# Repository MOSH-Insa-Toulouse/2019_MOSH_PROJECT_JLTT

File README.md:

# 2019_MOSH_PROJECT_JLTT : Kicad and Arduino LoraProject for SMART GAS sensor
> Loan Revardel / Jérémy Turi / Théo Zanchi / Thomas Lautrédou

#### <em> Key-words: </em> ```Arduino```, ```KiCad```, ```The Thing Network```, ```LoRa```, ```Node-RED```, ```IoT```, ```Gas sensor```.

This project was carried out as part of ISS (Innovative Smart Systems) 5th year at INSA Toulouse. The objective was to develop a gas sensor able to detect dangerous gases for human beings and communicating datas via Lora. Then, using the Node-RED software, we retrieved the data and displayed it on a graphical interface that the user could understand. As soon as a dangerous gas is detected, a buzzer is triggered to warn the user and avoid potential casualties. 

# Content of the Project

This repository contains : 
<ul>
<li><strong>KiCad files</strong> : We developed a shield for the gas sensor compatible with Arduino Uno (using <a href="http://kicad-pcb.org/">KiCad</a>) </li>
<li><strong>Arduino SW files</strong> : The source code we implemented on the microcontroller <a href="https://fr.rs-online.com/web/p/products/7589339?cm_mmc=FR-PLA-DS3A-_-google-_-CSS_FR_FR_(FR:Whoop!)+Semi-conducteurs_Control-_-(FR:Whoop!)+Kits+de+d%C3%A9veloppement+pour+processeurs+et+microcontr%C3%B4leurs-_-PRODUCT_GROUP&matchtype=&pla-391040009911&gclid=CjwKCAiAlO7uBRANEiwA_vXQ-7CN3iR2N3csU5tjIIjQNIGa3bsX8twG7D_S9v6flhEkI08b6nLumxoCnKcQAvD_BwE&gclsrc=aw.ds"> ATMEGA328 </a> (using <a href="https://www.arduino.cc/">Arduino IDE</a>)</li>
<li>A <strong>Node-RED dashboard</strong> to display datas retrieved from the gas sensor (using <a href="https://nodered.org/">Node-RED</a>)</li>
</ul>

# Overall components presentation
The goal of the project was to develop a prototype able to detect high dangerous gas concentration in a specific area. In this situation, a siren is triggered to alert people and avoid casualties. 

To do so, we used :
<ul>
<li>A <a href="https://store.arduino.cc/arduino-uno-rev3">Arduino Uno Board</a></li>
<li>A LoRa chip <a href="https://www.microchip.com/wwwproducts/en/RN2483">RN2483A</a></li>
<li>A <a href="http://wiki.seeedstudio.com/Grove-Gas_Sensor-MQ9/">Grove Gas Sensor (MQ9)</a></li>
<li>A potentiometer</li>
<li>A transistor <a href="http://www.vishay.com/docs/91291/91291.pdf">IRFZ44</a></li>
</ul>

### Dashboard

Then after creating a TTN application and registering our device, we used a ttn uplink node to receive the data sent to our TTN application. Finally, with some basic functions and chart blocs, we were able to display in a dashboard all the data in real time. You can find on the following figures the Node-Red flow and dashboard:

### Energy consumption

During our smart device realization, we studied the energy consumption in order to optimize it. We found that we were consuming 355mA and 370mA during an emission. That is why we chose to define a sleep cycle. Indeed, every 8 seconds, our smart device wake up, read the sensor value and send it to TTN. To realize this, we used an Arduino library by convenience and lack of time:

This sleep cycle allows a great reduction of energy consumption and an increasing of battery lifetime.

## KiCad

In this repository, you can find KiCad files of our project. We designed an Arduino shield based on the sensor we produced at the AIME laboratory. This shield is composed of the sensor, a buzzer, a NRF2483 LoRa ship and an adapter circuit for the gas sensor. You can see on the following figure the schematics we designed with KiCad:

After the schematics design, we exported the net file and realized the PCB routing that you can find with the following figures:

Finally, we exported a 3d representation of our shield thanks to KiCad:

## Conclusion

During this whole module, we were able to realize an electronic product from scratch. Indeed, from the sensor creation to the shield design and software programming, we had to mobilize several skills. Our team was composed of people with different background. That point helped us to dispatch the tasks and learn from the other experience.

To improve our project, we could for example design a PCB of a smaller size by using SMD instead of through-hole ones. Also, our PCB is only composed of the sensing and acting part of the device, a great think can be to integrate directly a micro-controller like an atmega328p in our PCB. The question of the battery and energy harvesting can be also asked and finally, we can use, to develop the dashboard, a different technology instead of Node-Red which is quite limiting.

To conclude, the whole process of sensor creation at the AIME, the PCB design with KiCad and the building of smart device during the MOSH module was a really interesting project related to IOT.

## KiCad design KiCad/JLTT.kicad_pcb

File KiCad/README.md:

# 2019_MOSH_PROJECT_JLTT : Kicad and Arduino LoraProject for SMART GAS sensor
> Loan Revardel / Jérémy Turi / Théo Zanchi / Thomas Lautrédou

#### <em> Key-words: </em> ```Arduino```, ```KiCad```, ```The Thing Network```, ```LoRa```, ```Node-RED```, ```IoT```, ```Gas sensor```.

This project was carried out as part of ISS (Innovative Smart Systems) 5th year at INSA Toulouse. The objective was to develop a gas sensor able to detect dangerous gases for human beings and communicating datas via Lora. Then, using the Node-RED software, we retrieved the data and displayed it on a graphical interface that the user could understand. As soon as a dangerous gas is detected, a buzzer is triggered to warn the user and avoid potential casualties. 

# Content of the Project

This repository contains : 
<ul>
<li><strong>KiCad files</strong> : We developed a shield for the gas sensor compatible with Arduino Uno (using [KiCad](http://kicad-pcb.org/))</li>
<li><strong>Arduino SW files</strong></li>
<li>A <strong>Node-RED dashboard</strong> to display datas retrieved from the gas sensor</li>
</ul>

Conso : 355mA (fonctionnement normal) et 370mA (fonctionnement en émission)

Il faut mettre un Nmos en Not Gate => Quand y'a un 0 le transistor est ouvert et le gaz sensor est relié à Vdd grâce à la résistance de pull-up, et quand on met 1 le transistor est passant et donc la tension aux bornes du Gaz sensor est amenée à 0.

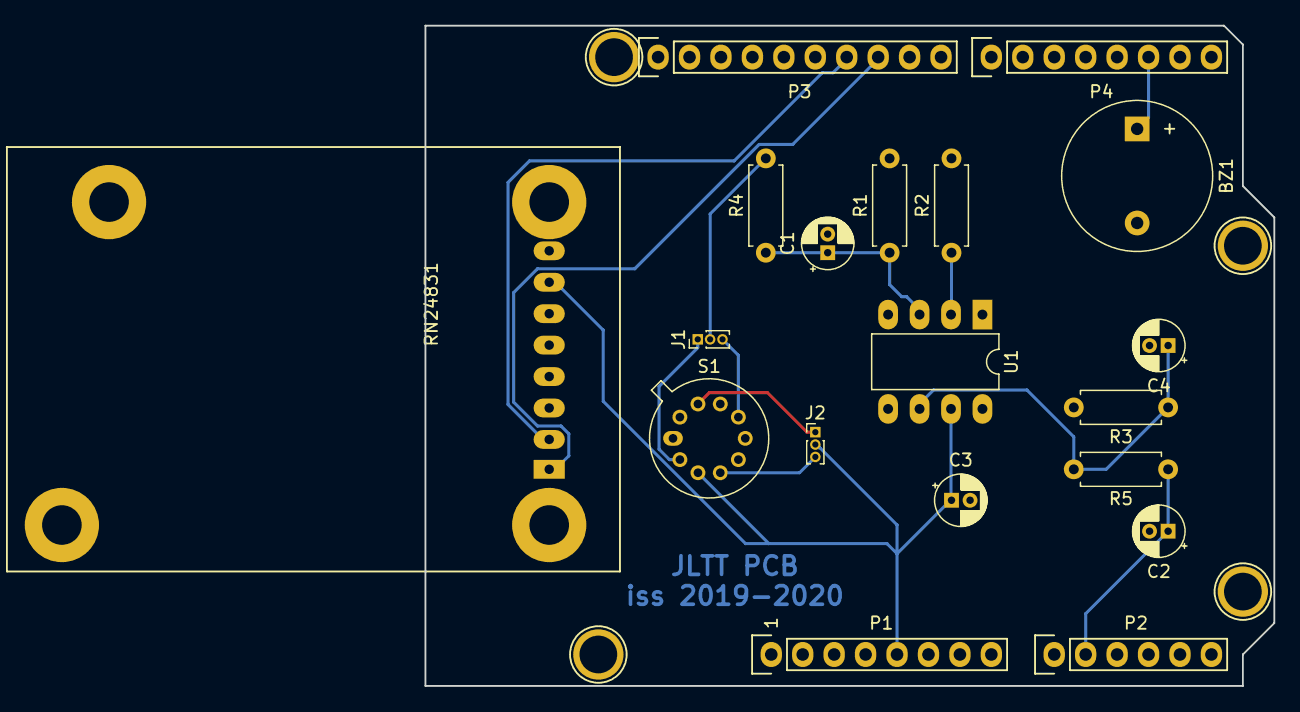
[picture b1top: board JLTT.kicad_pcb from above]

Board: 2 copper layers, 68.6 x 53.3 mm, 23 parts (0 on the bottom side), 16 nets.

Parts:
BZ1: Buzzer; Buzzer_12x9.5RM7.6
C1, C2, C3: 100n; CP_Radial_D4.0mm_P1.50mm
C4: 1µ; CP_Radial_D4.0mm_P1.50mm
J1, J2: Conn_01x03; PinHeader_1x03_P1.00mm_Vertical
P1: Power; Socket_Strip_Arduino_1x08
P2: Analog; Socket_Strip_Arduino_1x06
P3: Digital; Socket_Strip_Arduino_1x10
P4: Digital; Socket_Strip_Arduino_1x08
P5, P6, P7, P8: CONN_01X01; Arduino_1pin
R1, R3: 100k; R_Axial_DIN0207_L6.3mm_D2.5mm_P7.62mm_Horizontal
R2, R5: 1k; R_Axial_DIN0207_L6.3mm_D2.5mm_P7.62mm_Horizontal
R4: 10k; R_Axial_DIN0207_L6.3mm_D2.5mm_P7.62mm_Horizontal
RN24831: RN2483; RN2483_breakout
S1: capteur_gaz_aime; TO-5-10_Window
U1: LTC1050; DIP-8_W7.62mm_LongPads

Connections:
+5V: C3.1, J2.2, P1.5, RN24831.7, S1.3, U1.7
/2: BZ1.1, P4.6
/10: P3.8, RN24831.1
/11: P3.7, RN24831.2
/A1: C2.1, P2.2, R5.1
/A4(SDA): P2.5, P3.2
/A5(SCL): P2.6, P3.1
/GasSelected1: J1.2, R4.2
/GasSensorLeft1: J1.1, S1.2
/GasSensorLeft2: J2.3, S1.4
/GasSensorRight1: J1.3, S1.7
/GasSensorRight2: J2.1, S1.9
GND: BZ1.2, C1.2, C2.2, C3.2, C4.2, P1.6, P1.7, P3.4, R1.2, R2.2, R3.2, RN24831.8, S1.5, S1.8, S1.10, U1.4
unnamed: C1.1, R1.1, R4.1, U1.3
unnamed: C4.1, R3.1, R5.2, U1.6
unnamed: R2.1, U1.2

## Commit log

2019-11-15 First commit arduino
2019-11-18 Setup
2019-11-18 test transmission
2019-11-18 Rajout capteur de gaz
    Capteur de gaz input sur A1
2019-11-18 New function to send message sendValueGasSensor()
    The function was previously directly in the loop function, it is now at the end of the file.
2019-11-18 Mise à jour du README.md du 18/11/2019
2019-11-25 MaJ test
2019-11-25 test
2019-11-25 Lien hypertexte KiCad
2019-11-25 Content Maj
2019-11-25 Ajout d'images
2019-11-25 Sleep time arduino
2019-11-25 Sleep library
2019-11-25 Maj Overall Presentation
2019-11-25 Maj Overall Pres => ajout de l'image
2019-12-28 PCB routing
2019-12-28 PCB copper gnd
2019-12-28 KiCad and Screens adding
2019-12-28 remove kicad
2019-12-28 Add kicad
2019-12-28 Finallize README
2019-12-28 folder fix
2019-12-28 README fix
2019-12-28 minor fix
2020-01-21 libs
2020-01-22 Update files for Kicad
